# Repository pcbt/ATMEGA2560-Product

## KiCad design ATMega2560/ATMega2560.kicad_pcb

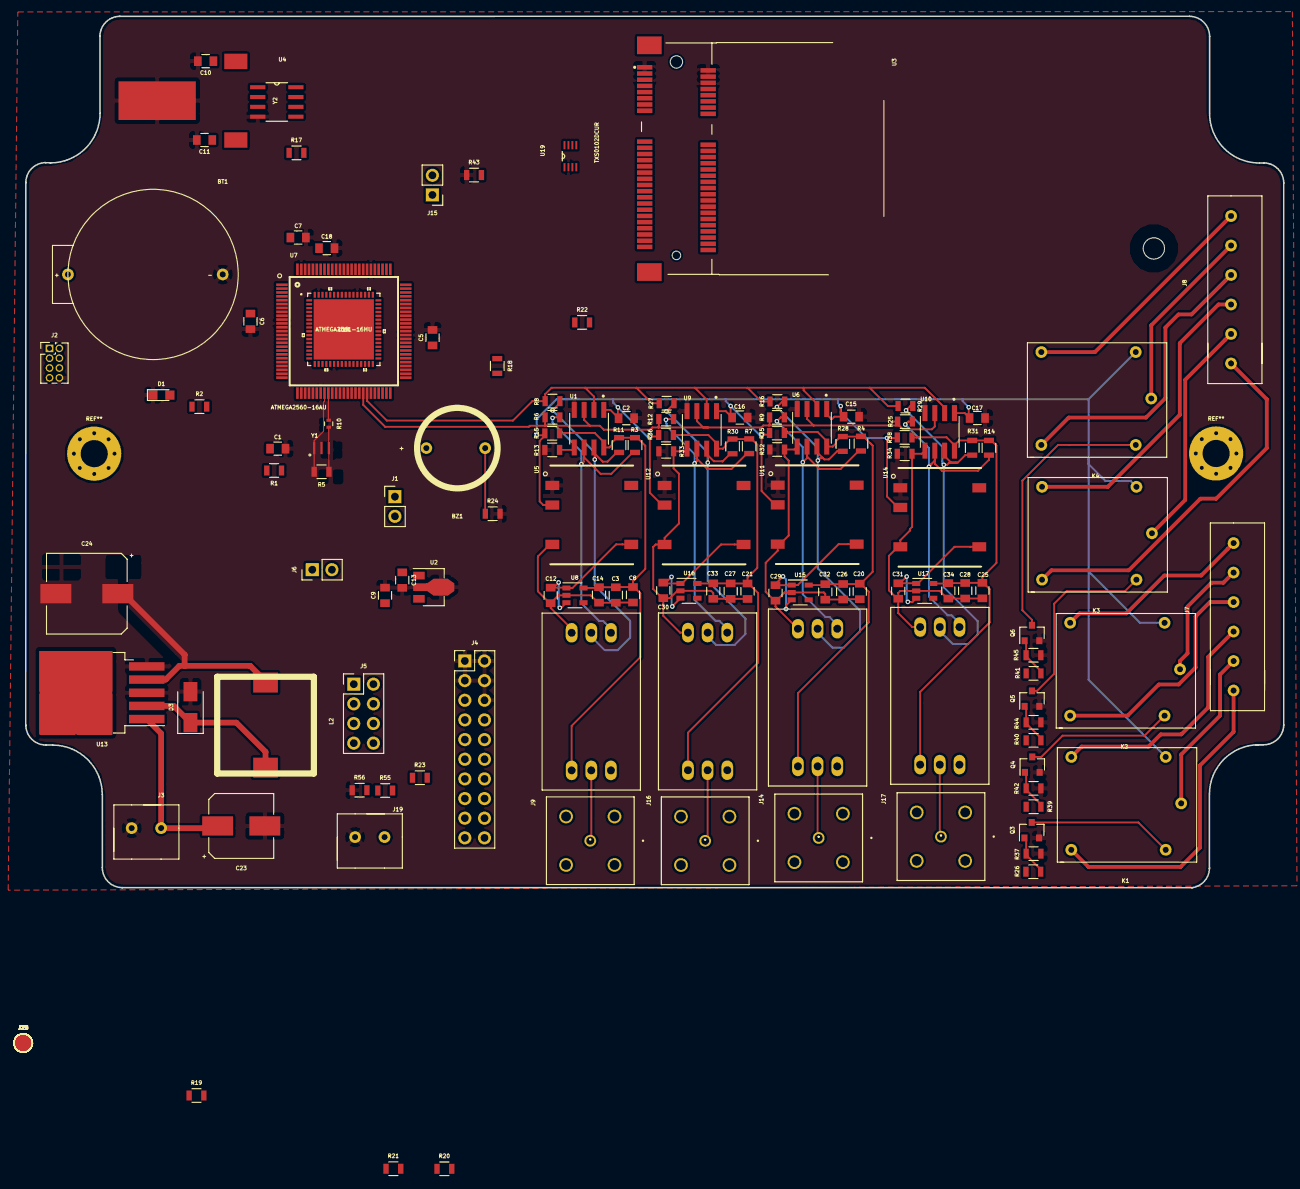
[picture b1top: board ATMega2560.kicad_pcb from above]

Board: 2 copper layers, 162.5 x 112.6 mm, 141 parts (0 on the bottom side), 107 nets.

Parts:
BT1: Battery_Cell; DS1092-04-B6P
BZ1: Buzzer; MCW12075
C1, C10, C11: 22pF; C_0805
C2, C5, C6, C7, C8, C13, C15, C16, C17, C18, C20, C21, C25: 0.1uF; C_0805
C3, C12, C26, C27, C28, C29, C30, C31: 1uF; C_0805
C9: 0.33uF; C_0805
C14, C32, C33, C34: 2.2uF; C_0805
C23: 100uF; CP_Elec_8x10
C24: 1000uF; CP_Elec_10x10.5
D1: ON; LED_0805
D3: 3A-60V; D_SMA
EZ1, EZ2, EZ3, EZ4: EZO-hub; Atlas_Stamp
J1: RX/TX; Pin_Header_Straight_1x02_Pitch2.54mm
J2: Prog_02x04_Odd_Even; Pin_Header_Straight_2x04_Pitch1.27mm
J3: Power_IN_01x02; 15EDGVC-3.81-02P-14-00AH
J4: Sensors_02x10_Odd_Even; Pin_Header_Straight_2x10_Pitch2.54mm
J5: IO_02x04_Odd_Even; Pin_Header_Straight_2x04_Pitch2.54mm
J6: I2C; Pin_Header_Straight_1x02_Pitch2.54mm
J7, J8: Screw_Terminal_01x06; 15EGTVC-3.81-06P-14-00AH
J9, J14, J16, J17: BNC_1; 5-1634503-1
J10: TEST_VBat; TestPoint_Pad_D2.0mm
J11: TEST_Reset; TestPoint_Pad_D2.0mm
J12: TEST_MISO; TestPoint_Pad_D2.0mm
J13: TEST_5V; TestPoint_Pad_D2.0mm
J15: BTN; Pin_Header_Straight_1x02_Pitch2.54mm
J18: TEST_MOSI; TestPoint_Pad_D2.0mm
J19: Analog_IN_01x02; 15EDGVC-3.81-02P-14-00AH
J20: TEST_3.3V; TestPoint_Pad_D2.0mm
J21: TEST_SCK; TestPoint_Pad_D2.0mm
J22: TEST_GND; TestPoint_Pad_D2.0mm
J23: TEST_RX0; TestPoint_Pad_D2.0mm
J24: TEST_TX0; TestPoint_Pad_D2.0mm
J25: TEST_VDD_EXT; TestPoint_Pad_D2.0mm
K1, K2, K3, K4: G5Q-1; HJR-3FF-S-Z-4
L2: 100uH; L_SMD_12.5x12.5
Q3, Q4, Q5, Q6: NMOS; SOT-23
R1, R17, R37, R42, R43, R44, R45: 10K; R_0805
R2, R26, R39, R40, R41: 1K; R_0805
R3, R4, R7, R11, R14, R18, R22, R23, R28, R30, R31: 4.7K; R_0805
R5, R55: 1M; R_0805
R6, R8, R9, R12, R13, R15, R16, R25, R27, R29, R32, R33, R34, R35, R36, R38: DNP; R_0805
R10: 27R; R_0402
R19, R20, R21, R24: 100R; R_0805
R56: 100K; R_0805
U1, U6, U9, U10: SI8600; SOIC127P600X175-8N
U2: L78L33ABUTR; SOT-89-3
U3: MPCIE-Socket; TE_2041119-1
U4: DS1302; SOIC127P600X175-8N
U5, U11, U12, U14: R1SE-0505; SOIC254P1110X700-5N
U7: ATMEGA2560-16AU; QFP50P1600X1600X120-100N
U8, U15, U16, U17: LD2981ABM; SOT-23-5
U13: LM2576; TO-263-5_TabPin3
U18: ATMEGA2561-16MU; ATMEGA2561V-8MU
U19: TXS0102DCUR; SOP50P310X90-8N
Y1: 16Mhz; OSC_CSTCE16M0V53-R0
Y2: 32.768 KHz; R38-32.768

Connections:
+3.3V: C13.1, J4.15, J20.1, U2.1
+5V: C2.2, C5.1, C6.1, C7.1, C9.1, C15.2, C16.2, C17.2, C24.1, J2.6, J4.17, J4.18, J4.19, J4.20, J13.1, J15.1, K1.5, K2.5, K3.5, K4.5, L2.2, R1.1, R2.1, R15.2, R18.1, R22.1, R23.1, R35.2, R36.2, R38.2, U1.1, U2.3, U4.1, U5.2, U6.1, U7.10, U7.31, U7.61, U7.80, U7.100, U9.1, U10.1, U11.2, U12.2, U13.4, U14.2, U18.21, U18.52, U18.64, U19.7
/A0: J5.8, R55.1, R56.2, U7.97, U18.61
/A1: J5.6, U7.96, U18.60
/A2: J5.4, U7.95, U18.59
/A3: J5.2, U7.94, U18.58
/ARD_MISO: J2.5, J12.1, U7.22, U18.13
/ARD_MOSI: J2.3, J18.1, U7.21, U18.12
/ARD_SCK: J2.1, J21.1, U7.20, U18.11
/AREF: C18.1, U7.98, U18.62
/BUZZER: BZ1.1, U7.71, U18.44
/D2: R26.1, U7.6, U18.6
/D3: R39.1, U7.7, U18.7
/D4: R40.1, U7.1
/D5: R41.1, U7.5, U18.5
/D25: J5.1, U7.75, U18.48
/D26: J5.3, U7.74, U18.47
/D27: J5.5, U7.73, U18.46
/D28: J5.7, J15.2, R43.2, U7.72, U18.45
/DS18B20: J4.16, R23.2, U7.26, U18.17
/GND_ISO1: C3.1, C8.1, C12.1, C14.2, EZ1.1, R13.1, U1.5, U5.4, U8.2
/GND_ISO2: C21.1, C27.1, C30.1, C33.2, EZ3.1, R33.1, U9.5, U12.4, U16.2
/GND_ISO3: C20.1, C26.1, C29.1, C32.2, EZ2.1, R32.1, U6.5, U11.4, U15.2
/GND_ISO4: C25.1, C28.1, C31.1, C34.2, EZ4.1, R34.1, U10.5, U14.4, U17.2
/PIR_DL: J4.11, U7.19, U18.10
/PIR_SERIN: R19.1, U7.25, U18.16
/PIR_SERIN_REG: J4.13, R19.2, R20.1
/PWR_CNTRL: U3.8, U7.78, U18.51
/PWR_KEY: U3.10, U7.77, U18.50
/RESET: C1.1, J2.7, J11.1, R1.2, U7.30, U18.20
/RTC_CE: U4.5, U7.53, U18.35
/RTC_MISO: R17.1, U4.6, U7.59, U18.41
/RTC_MOSI: R17.2, U7.57, U18.39
/RTC_SCLK: U4.7, U7.55, U18.37
/RX0: J2.2, J23.1, U7.2, U18.2
/RX1: J1.2, U7.45, U18.27, U19.1
/SCREEN_RX: J4.7, U7.24, U18.15
/SCREEN_TX: J4.9, U7.23, U18.14
/TX0: J2.4, J24.1, U7.3, U18.3
/TX1: J1.1, U7.46, U18.28, U19.8
/UART1_DTR: U3.19, U7.76, U18.49
/UART1_RXD: U3.27, U19.5
/UART1_TXD: U3.25, U19.4
/US1_ECHO: J4.10, U7.17, U18.8
/US1_TR: J4.8, U7.18, U18.9
/US2_ECHO: J4.14, U7.15
/US2_TR: J4.12, U7.16
/VDD_EXT: J25.1, U3.12, U19.3, U19.6
/VDD_ISO1: C3.2, C8.2, C14.1, EZ1.4, R3.1, R11.1, R15.1, U1.8, U8.5
/VDD_ISO2: C21.2, C27.2, C33.1, EZ3.4, R7.1, R30.1, R36.1, U9.8, U16.5
/VDD_ISO3: C20.2, C26.2, C32.1, EZ2.4, R4.1, R28.1, R35.1, U6.8, U15.5
/VDD_ISO4: C25.2, C28.2, C34.1, EZ4.4, R14.1, R31.1, R38.1, U10.8, U17.5
/XTAL+: R10.1, U7.34, U18.24
/XTAL-: R5.2, U7.33, U18.23, Y1.1
GND: BT1.2, C1.2, C2.1, C5.2, C6.2, C7.2, C9.2, C10.2, C11.2, C13.2, C15.1, C16.1, C17.1, C18.2, C23.2, C24.2, D1.1, D3.2, J2.8, J3.2, J4.1, J4.2, J4.3, J4.4, J4.6, J19.2, J22.1, Q3.2, Q4.2, Q5.2, Q6.2, R13.2, R21.2, R24.2, R32.2, R33.2, R34.2, R37.1, R42.1, R43.1, R44.1, R45.1, R56.1, U1.4, U2.2, U3.1, U3.2, U3.3, U3.4, U3.5, U3.6, U4.4, U5.1, U6.4, U7.11, U7.32, U7.62, U7.81, U7.99, U9.4, U10.4, U11.1, U12.1, U13.3, U13.5, U14.1, U18.22, U18.53, U18.63, U19.2, Y1.2, Y2.2
unnamed: BT1.1, U4.8
unnamed: BZ1.2, R24.1
unnamed: C10.1, U4.2, Y2.3
unnamed: C11.1, U4.3, Y2.1
unnamed: C12.2, U5.5, U8.1, U8.3
unnamed: C29.2, U11.5, U15.1, U15.3
unnamed: C30.2, U12.5, U16.1, U16.3
unnamed: C31.2, U14.5, U17.1, U17.3
unnamed: D1.2, R2.2
unnamed: D3.1, L2.1, U13.2
unnamed: EZ1.2, R8.1, R11.2, U1.7
unnamed: EZ1.3, R3.2, R6.2, U1.6
unnamed: EZ1.5, J9.1
unnamed: EZ1.6, J9.2
unnamed: EZ2.2, R16.1, R28.2, U6.7
unnamed: EZ2.3, R4.2, R9.2, U6.6
unnamed: EZ2.5, J14.1
unnamed: EZ2.6, J14.2
unnamed: EZ3.2, R27.1, R30.2, U9.7
unnamed: EZ3.3, R7.2, R12.2, U9.6
unnamed: EZ3.5, J16.1
unnamed: EZ3.6, J16.2
unnamed: EZ4.2, R29.1, R31.2, U10.7
unnamed: EZ4.3, R14.2, R25.2, U10.6
unnamed: EZ4.5, J17.1
unnamed: EZ4.6, J17.2
unnamed: J7.1, K2.4
unnamed: J7.2, K2.2
unnamed: J7.3, K2.3
unnamed: J7.4, K1.4
unnamed: J7.5, K1.2
unnamed: J7.6, K1.3
unnamed: J8.1, K4.4
unnamed: J8.2, K4.2
unnamed: J8.3, K4.3
unnamed: J8.4, K3.4
unnamed: J8.5, K3.2
unnamed: J8.6, K3.3
unnamed: J19.1, R55.2
unnamed: K1.1, Q3.3
unnamed: K2.1, Q4.3
unnamed: K3.1, Q5.3
unnamed: K4.1, Q6.3
unnamed: Q3.1, R26.2, R37.2
unnamed: Q4.1, R39.2, R42.2
unnamed: Q5.1, R40.2, R44.2
unnamed: Q6.1, R41.2, R45.2
unnamed: R5.1, R10.2, Y1.3
unnamed: R20.2, R21.1
SCL: J6.1, R6.1, R9.1, R12.1, R22.2, R25.1, U1.3, U6.3, U7.43, U9.3, U10.3, U18.25
SDA: J6.2, R8.2, R16.2, R18.2, R27.2, R29.2, U1.2, U6.2, U7.44, U9.2, U10.2, U18.26
VBat: C23.1, J3.1, J10.1, U3.11, U3.13, U3.15, U13.1

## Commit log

2018-05-28 sim800c seperated
2018-09-19 BNC, Relay and Regulator connections are made

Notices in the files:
parts and their libraries:
Copyright 2016 Accelerated Designs. All rights reserved.
